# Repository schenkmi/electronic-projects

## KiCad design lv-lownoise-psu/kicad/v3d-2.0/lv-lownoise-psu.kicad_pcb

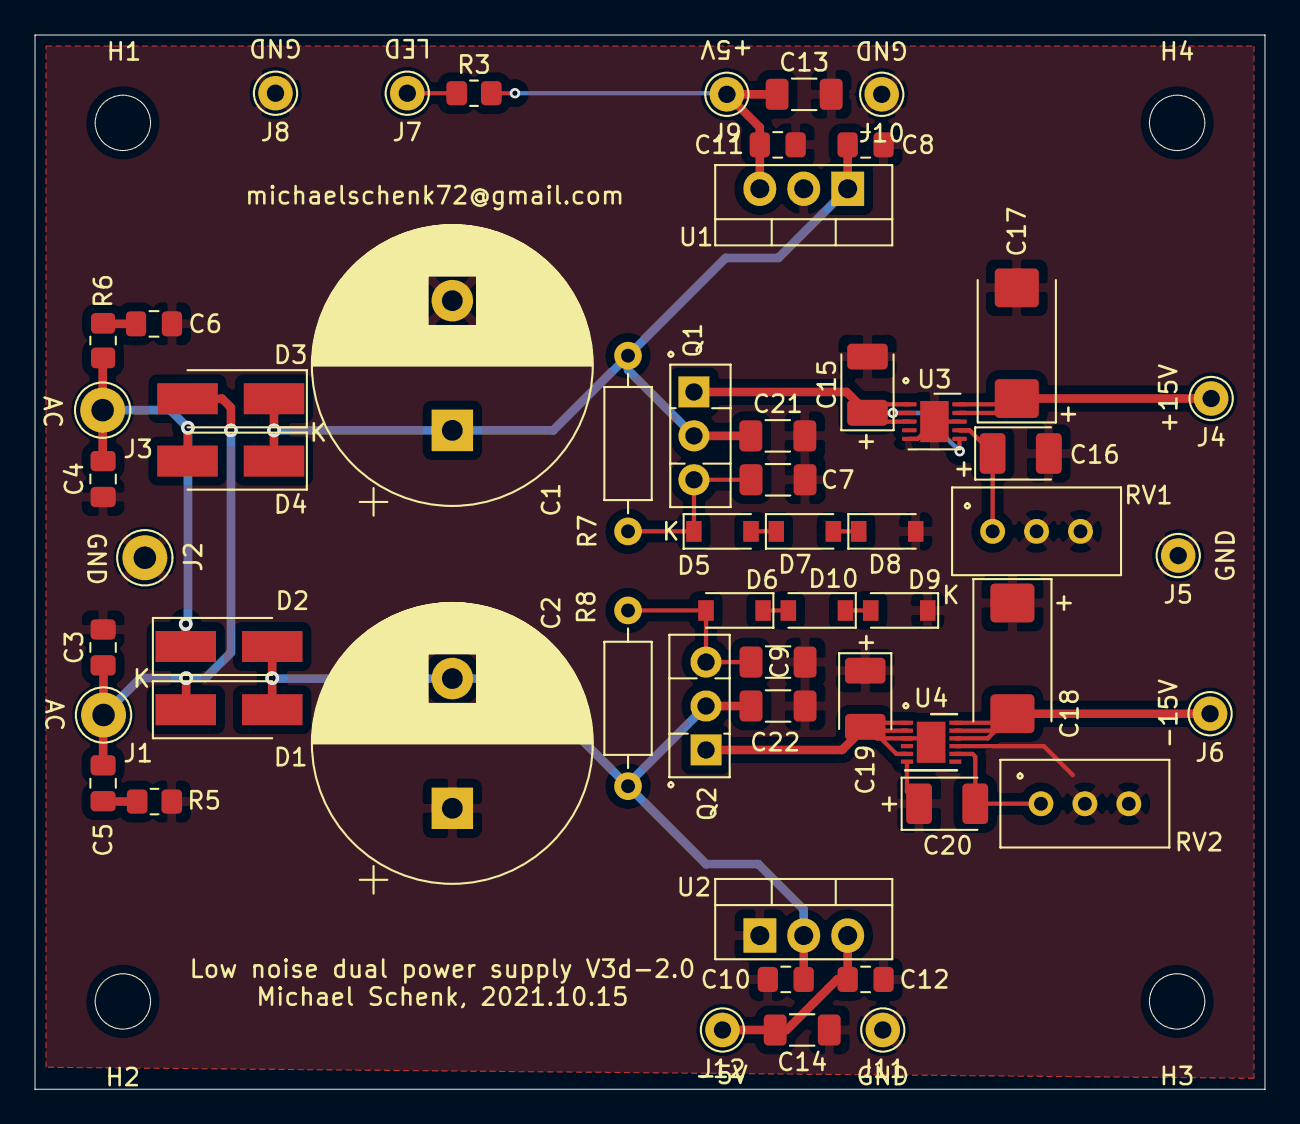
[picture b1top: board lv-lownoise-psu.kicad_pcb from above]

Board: 2 copper layers, 71.1 x 61.0 mm, 61 parts (0 on the bottom side), 22 nets.

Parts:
C1, C2: 2200uF; CP_Radial_D16.0mm_P7.50mm
C3, C4: Cx/10nF/50V; C_0805_2012Metric_Pad1.18x1.45mm_HandSolder
C5, C6: Cs/50V; C_0805_2012Metric_Pad1.18x1.45mm_HandSolder
C7, C9, C21, C22: 4.7uF/50V; C_1206_3216Metric_Pad1.33x1.80mm_HandSolder
C8, C10: 330nF; C_0805_2012Metric_Pad1.18x1.45mm_HandSolder
C11, C12: 100nF; C_0805_2012Metric_Pad1.18x1.45mm_HandSolder
C13, C14: 10uF/25V; C_1206_3216Metric_Pad1.33x1.80mm_HandSolder
C15, C16, C19, C20: 4.7uF/35V; CP_EIA-3528-15_AVX-H_Pad1.50x2.35mm_HandSolder
C17, C18: 33uF; CP_EIA-7343-31_Kemet-D_Pad2.25x2.55mm_HandSolder
D1, D2, D3, D4: BYG20D; D_SMA_Handsoldering
D5, D6, D7, D8, D9, D10: MMSZ5232B/5.6V; D_SOD-123
H1, H2, H3, H4: MountingHole; MountingHole_3.2mm_M3
J1, J3: AC; Pin_D1.3mm_L11.0mm
J2: GND; Pin_D1.3mm_L11.0mm
J4: +15V; Pin_D1.0mm_L10.0mm
J5, J8, J10, J11: GND; Pin_D1.0mm_L10.0mm
J6: -15V; Pin_D1.0mm_L10.0mm
J7: LED; Pin_D1.0mm_L10.0mm
J9: +5V; Pin_D1.0mm_L10.0mm
J12: -5V; Pin_D1.0mm_L10.0mm
Q1: BD139; TO-126-3_Vertical
Q2: BD140; TO-126-3_Vertical
R3: 240R; R_0805_2012Metric_Pad1.20x1.40mm_HandSolder
R5, R6: Rs/1/8W; R_0805_2012Metric_Pad1.20x1.40mm_HandSolder
R7, R8: 430R/0.6W; R_Axial_DIN0207_L6.3mm_D2.5mm_P10.16mm_Horizontal
RV1, RV2: 200k; Potentiometer_Bourns_3296W_Vertical
U1: LM7805_TO220; TO-220-3_Vertical
U2: LM7905_TO220; TO-220-3_Vertical
U3: LT3045xDD-10DFN; DFN-10-1EP_3x3mm_P0.5mm_EP1.65x2.38mm
U4: LT3094xDD-12DFN; DFN-12-1EP_3x3mm_P0.45mm_EP1.66x2.38mm

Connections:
GND: C1.2, C2.1, C3.2, C4.1, C6.1, C7.2, C8.2, C9.1, C10.1, C11.2, C12.1, C13.2, C14.1, C15.2, C16.2, C17.2, C18.1, C19.1, C20.1, C21.2, C22.1, D8.2, D9.1, J2.1, J5.1, J8.1, J10.1, J11.1, R5.2, RV1.2, RV1.3, RV2.2, RV2.3, U1.2, U2.1, U3.5, U3.8, U3.11, U4.6, U4.9
unnamed: C1.1, C8.1, C21.1, D3.1, D4.1, Q1.2, R7.1, U1.1
unnamed: C3.1, C5.1, D1.1, D3.2, J1.1
unnamed: C4.2, D2.1, D4.2, J3.1, R6.2
unnamed: C5.2, R5.1
unnamed: C6.2, R6.1
unnamed: C7.1, D5.1, Q1.3, R7.2
unnamed: C9.2, D6.2, Q2.3, R8.1
unnamed: C2.2, C10.2, C22.2, D1.2, D2.2, Q2.2, R8.2, U2.2
unnamed: C11.1, C13.1, J9.1, R3.2, U1.3
unnamed: C12.2, C14.2, J12.1, U2.3
unnamed: C15.1, Q1.1, U3.1, U3.2, U3.3, U3.6
unnamed: C16.1, RV1.1, U3.7
unnamed: C17.1, J4.1, U3.9, U3.10
unnamed: C18.2, J6.1, U4.10, U4.11, U4.12
unnamed: C19.2, Q2.1, U4.1, U4.2, U4.3, U4.5, U4.13
unnamed: C20.2, RV2.1, U4.8
unnamed: D5.2, D7.1
unnamed: D7.2, D8.1
unnamed: D9.2, D10.1
unnamed: D6.1, D10.2
unnamed: J7.1, R3.1
